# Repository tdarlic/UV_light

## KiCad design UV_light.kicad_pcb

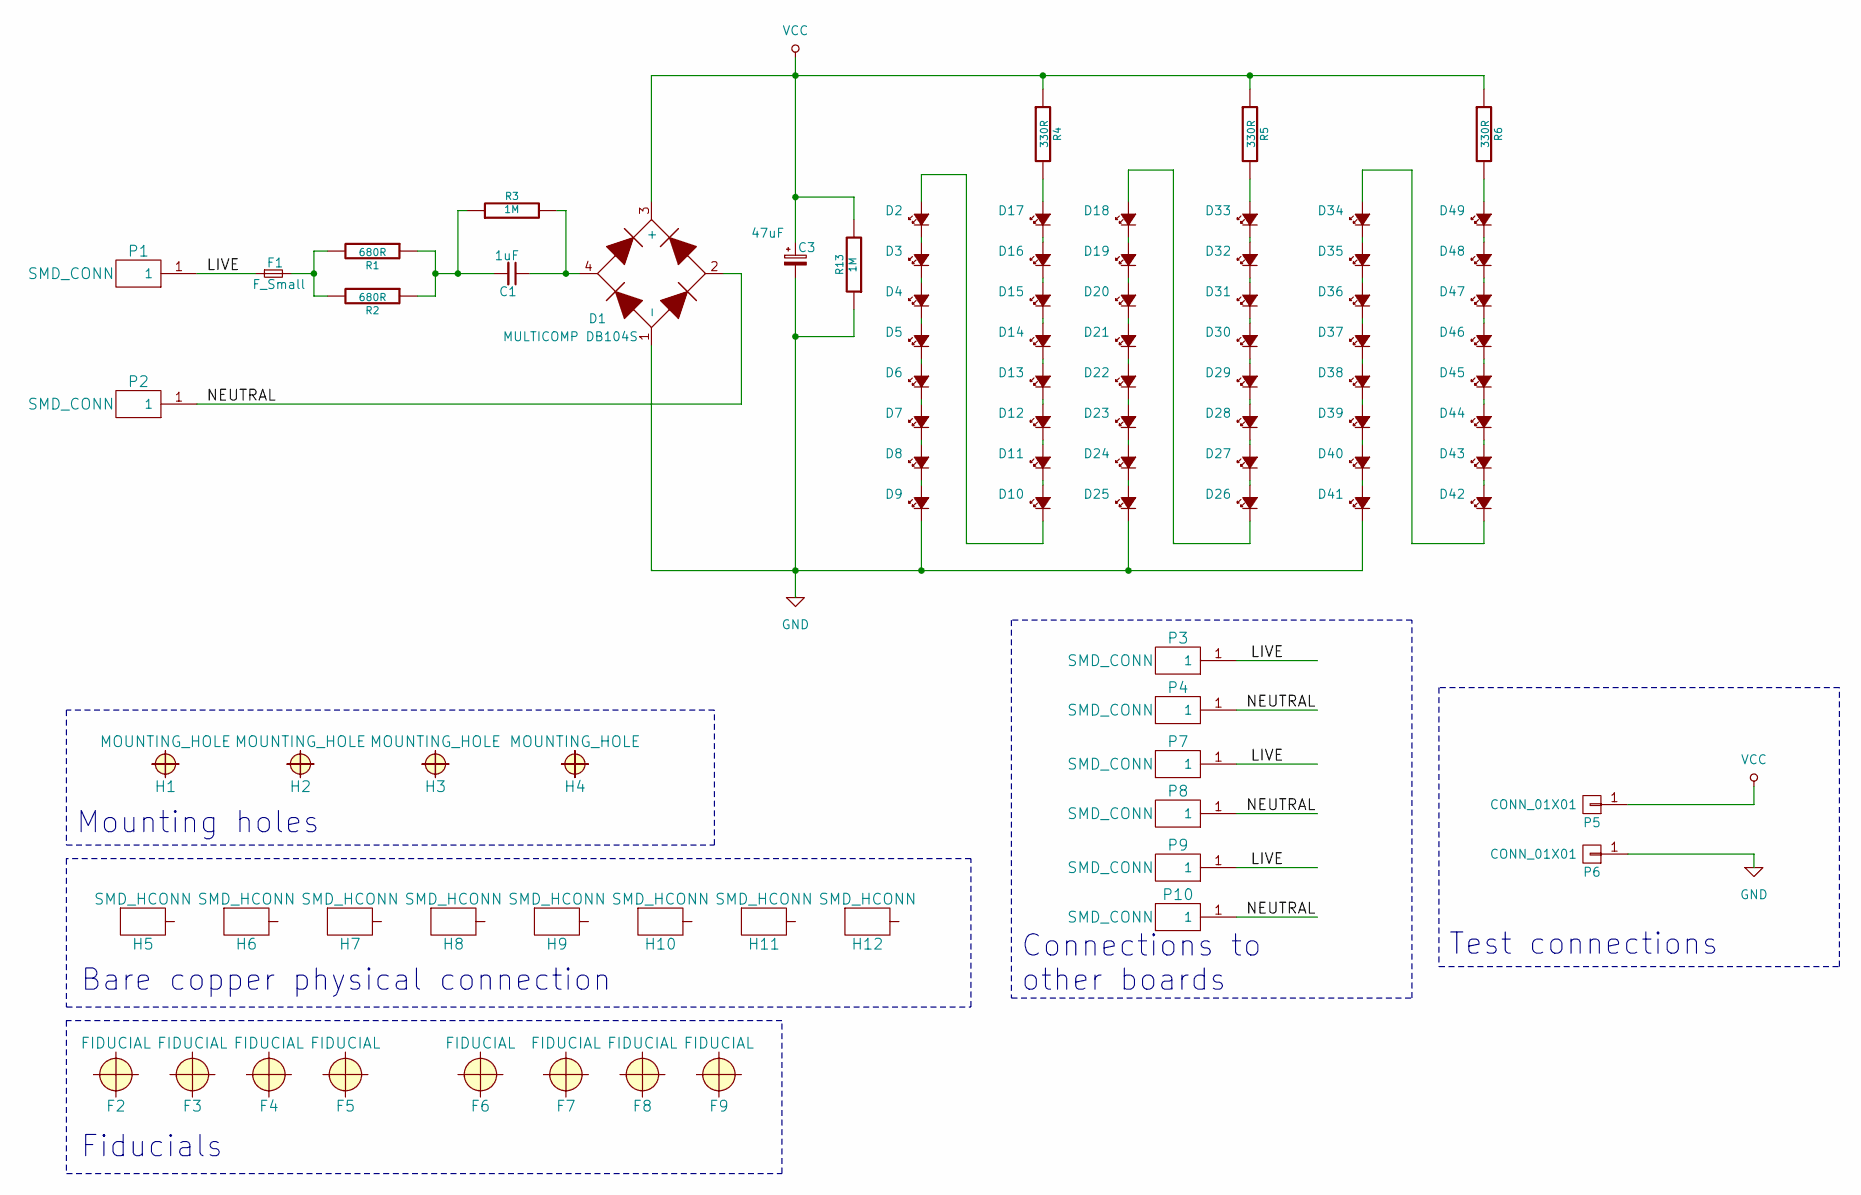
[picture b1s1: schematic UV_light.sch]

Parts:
C1: 1uF; Capacitor_film_26.5x10; Farnell code 2495926
C3: 47uF; Capacitor_Panasonic_G13; Farnell code 1973389
D1: MULTICOMP DB104S; DB104S; Farnell code 1861406
D2, D3, D4, D5, D6, D7, D8, D9, D10, D11, D12, D13, D14, D15, D16, D17, D18, D19, D20, D21, D22, D23, D24, D25, D26, D27, D28, D29, D30, D31, D32, D33, D34, D35, D36, D37, D38, D39, D40, D41, D42, D43, D44, D45, D46, D47, D48, D49: UV_LED; LED_3528
F1: F_Small; R_1206; Farnell code 1841065
F2, F3, F4, F5, F6, F7, F8, F9: FIDUCIAL
H1, H2, H3, H4: MOUNTING_HOLE; MountingHole_3-7mm
H5, H6, H7, H8, H9, H10, H11, H12: SMD_HCONN
P1, P2, P3, P4, P7, P8, P9, P10: SMD_CONN
P5, P6: CONN_01X01; TESTPOINT_SMD_3MM
R1, R2: 680R; R_2512; Farnell code 2117499
R3, R13: 1M; R_1206; Farnell code 9335781
R4, R5, R6: 330R; R_1206; Farnell code 2332133

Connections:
/LIVE: F1.1, P1.1, P3.1, P7.1, P9.1
/NEUTRAL: D1.2, P2.1, P4.1, P8.1, P10.1
GND: C3.2, D1.1 (-), D9.1 (K), D25.1 (K), D41.1 (K), P6.1, R13.1
unnamed: D2.1 (K), D3.2 (A)
unnamed: D3.1 (K), D4.2 (A)
unnamed: D4.1 (K), D5.2 (A)
unnamed: D5.1 (K), D6.2 (A)
unnamed: D6.1 (K), D7.2 (A)
unnamed: D7.1 (K), D8.2 (A)
unnamed: D8.1 (K), D9.2 (A)
unnamed: D2.2 (A), D10.1 (K)
unnamed: D10.2 (A), D11.1 (K)
unnamed: D11.2 (A), D12.1 (K)
unnamed: D12.2 (A), D13.1 (K)
unnamed: D13.2 (A), D14.1 (K)
unnamed: D14.2 (A), D15.1 (K)
unnamed: D15.2 (A), D16.1 (K)
unnamed: D16.2 (A), D17.1 (K)
unnamed: D17.2 (A), R4.2
unnamed: D18.1 (K), D19.2 (A)
unnamed: D18.2 (A), D26.1 (K)
unnamed: D19.1 (K), D20.2 (A)
unnamed: D20.1 (K), D21.2 (A)
unnamed: D21.1 (K), D22.2 (A)
unnamed: D22.1 (K), D23.2 (A)
unnamed: D23.1 (K), D24.2 (A)
unnamed: D24.1 (K), D25.2 (A)
unnamed: D26.2 (A), D27.1 (K)
unnamed: D27.2 (A), D28.1 (K)
unnamed: D28.2 (A), D29.1 (K)
unnamed: D29.2 (A), D30.1 (K)
unnamed: D30.2 (A), D31.1 (K)
unnamed: D31.2 (A), D32.1 (K)
unnamed: D32.2 (A), D33.1 (K)
unnamed: D33.2 (A), R5.2
unnamed: D34.1 (K), D35.2 (A)
unnamed: D34.2 (A), D42.1 (K)
unnamed: D35.1 (K), D36.2 (A)
unnamed: D36.1 (K), D37.2 (A)
unnamed: D37.1 (K), D38.2 (A)
unnamed: D38.1 (K), D39.2 (A)
unnamed: D39.1 (K), D40.2 (A)
unnamed: D40.1 (K), D41.2 (A)
unnamed: D42.2 (A), D43.1 (K)
unnamed: D43.2 (A), D44.1 (K)
unnamed: D44.2 (A), D45.1 (K)
unnamed: D45.2 (A), D46.1 (K)
unnamed: D46.2 (A), D47.1 (K)
unnamed: D47.2 (A), D48.1 (K)
unnamed: D48.2 (A), D49.1 (K)
unnamed: D49.2 (A), R6.2
unnamed: F1.2, R1.2, R2.2
VCC: C3.1, D1.3 (+), P5.1, R4.1, R5.1, R6.1, R13.2

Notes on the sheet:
Test connections
Connections to other boards
Mounting holes
Bare copper physical connection
Fiducials

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
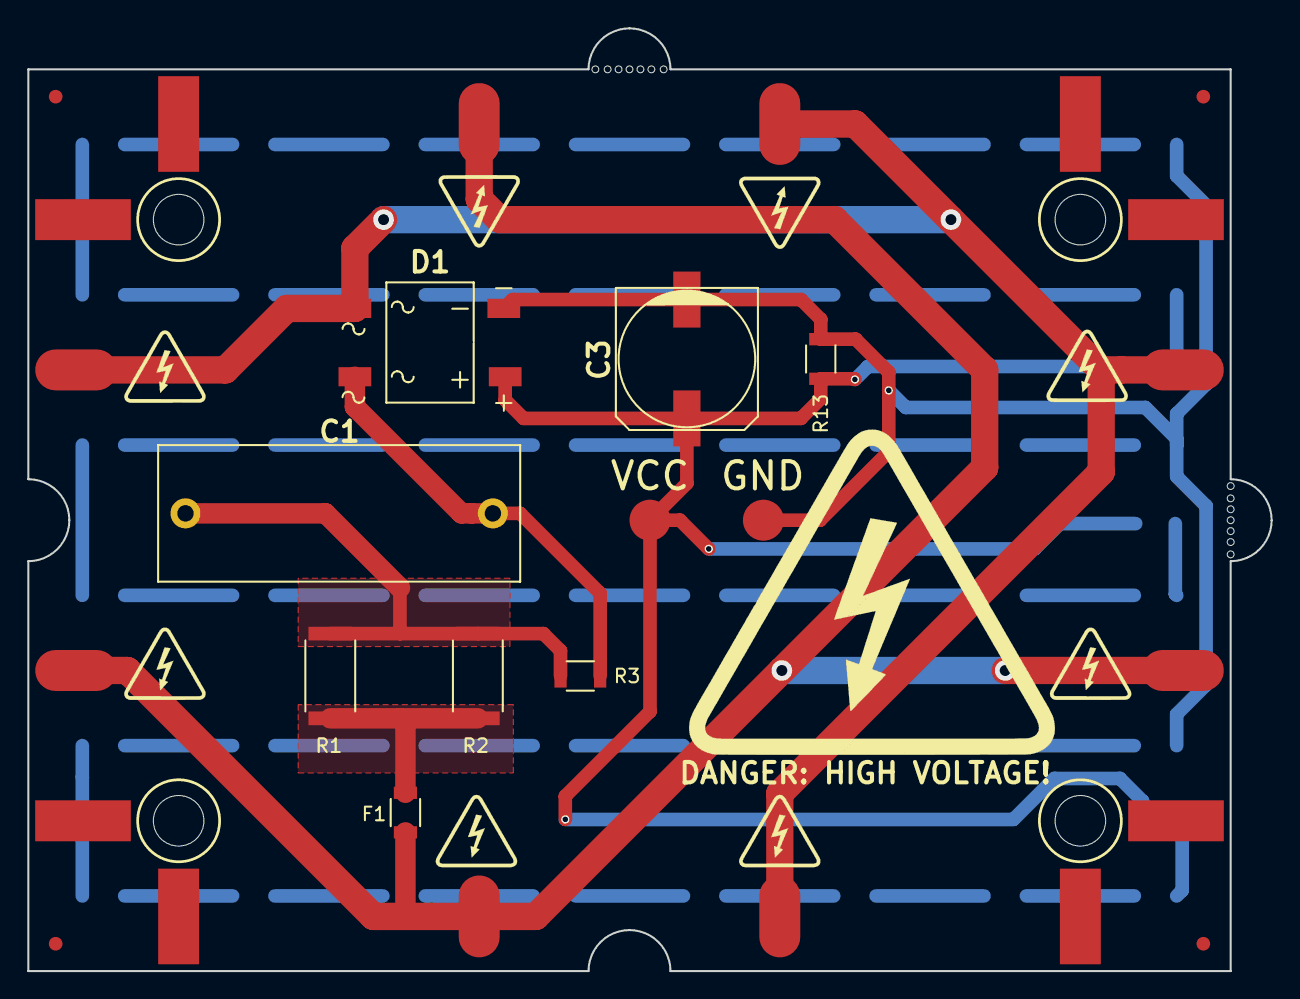
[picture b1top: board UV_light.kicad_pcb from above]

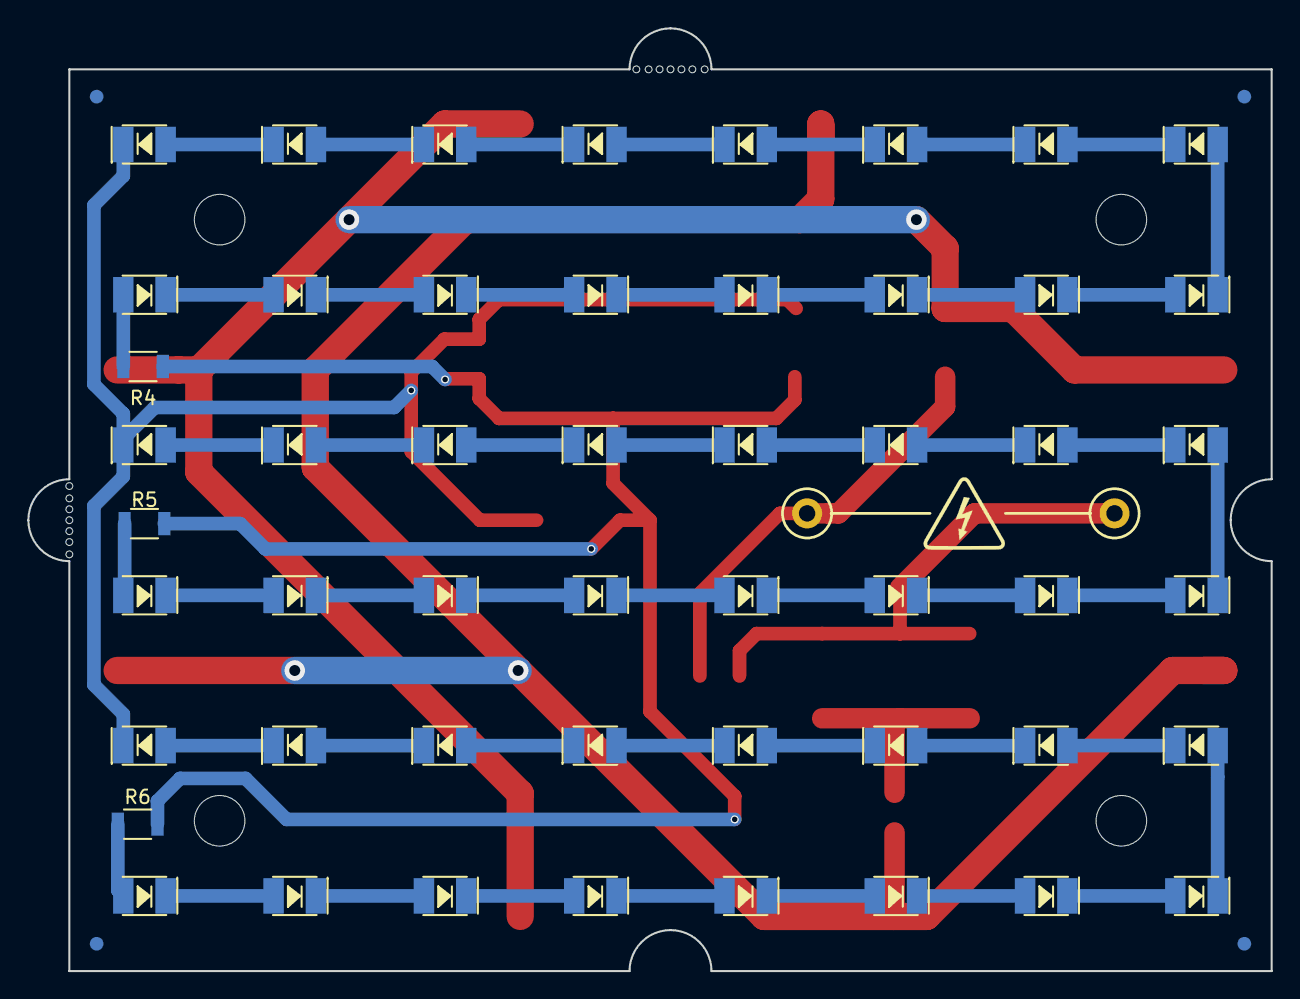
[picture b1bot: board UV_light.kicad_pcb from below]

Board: 2 copper layers, 91.0 x 69.0 mm, 89 parts (55 on the bottom side), 55 nets.

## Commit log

2016-09-12 :neckbeard: Added .gitattributes & .gitignore files
2016-09-12 Innitial commit
2016-10-31 Comleting version 2
2020-10-05 Adding ltspice simulation files
